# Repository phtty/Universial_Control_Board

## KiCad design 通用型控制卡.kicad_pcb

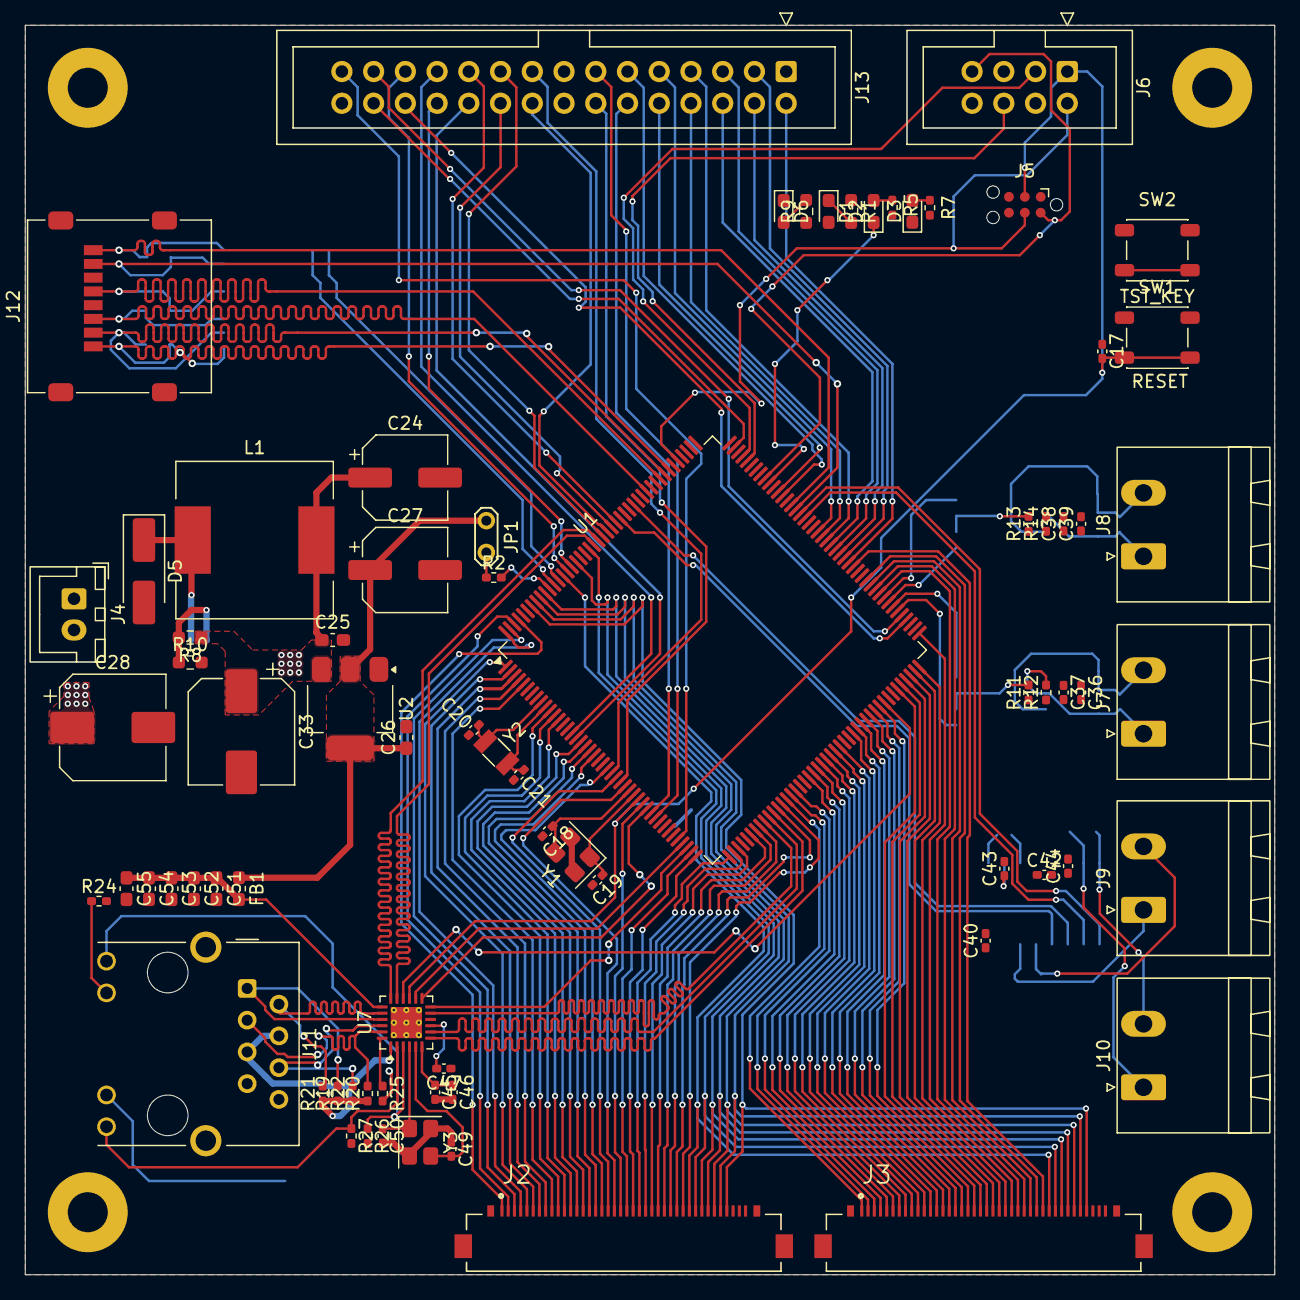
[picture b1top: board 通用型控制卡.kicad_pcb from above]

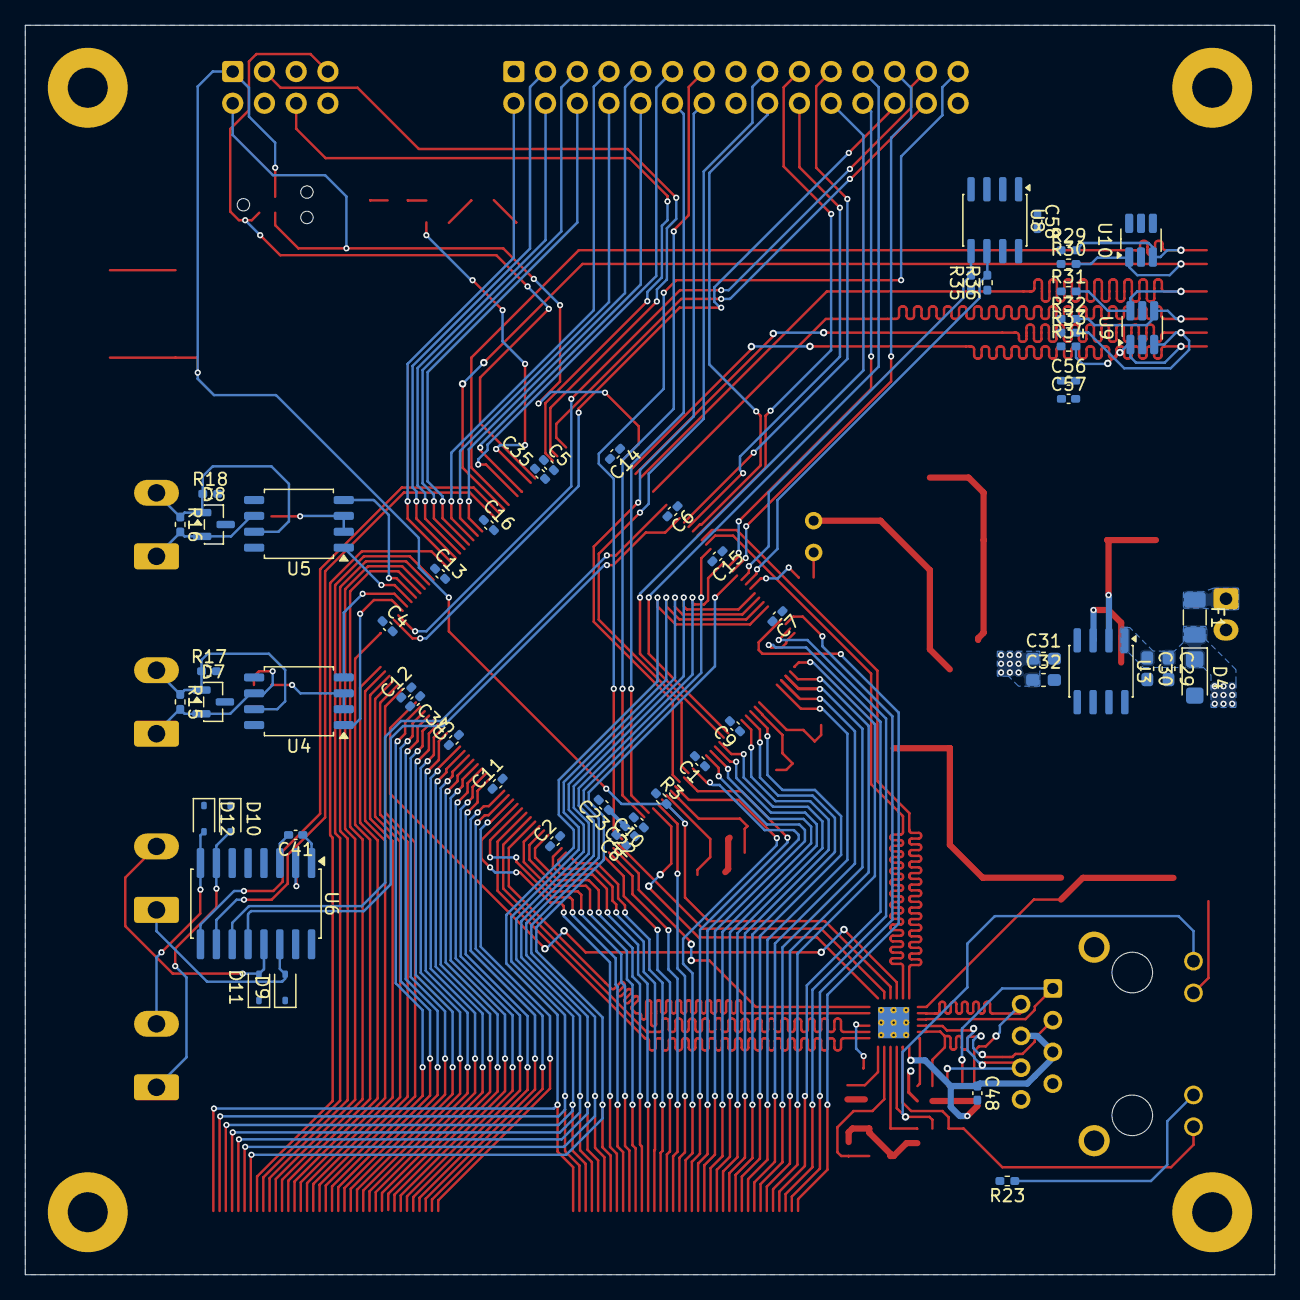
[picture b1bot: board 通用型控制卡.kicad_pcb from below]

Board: 4 copper layers, 100.0 x 100.0 mm, 138 parts (58 on the bottom side), 175 nets.

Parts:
C1, C2, C3, C4, C5, C6, C7, C8, C9, C10, C11, C12, C13, C14, C15, C16, C17, C23, C37, C39, C40, C41, C42, C43, C44, C47, C48, C56, C58: 100nF; C_0402_1005Metric_Pad0.74x0.62mm_HandSolder
C18, C19, C20, C21, C49, C50: 22pF; C_0402_1005Metric_Pad0.74x0.62mm_HandSolder
C22, C34, C35: 2.2uF; C_0402_1005Metric_Pad0.74x0.62mm_HandSolder
C24: 10uF/16V; CP_Elec_6.3x5.9
C25, C26: 100nF/16V; C_0603_1608Metric_Pad1.08x0.95mm_HandSolder
C27: 22uF/16V; CP_Elec_6.3x5.9
C28, C33: 220uF/35V; CP_Elec_8x10
C29: 10uF/35V; C_0603_1608Metric_Pad1.08x0.95mm_HandSolder
C30: 100nF/35V; C_0603_1608Metric_Pad1.08x0.95mm_HandSolder
C31, C51, C53, C54, C55: 100nF; C_0603_1608Metric_Pad1.08x0.95mm_HandSolder
C32: 22uF; C_0603_1608Metric_Pad1.08x0.95mm_HandSolder
C36, C38, C57: 10uF; C_0402_1005Metric_Pad0.74x0.62mm_HandSolder
C45: 471; C_0402_1005Metric_Pad0.74x0.62mm_HandSolder
C46: 1uF; C_0402_1005Metric_Pad0.74x0.62mm_HandSolder
C52: 10uF; C_0603_1608Metric_Pad1.08x0.95mm_HandSolder
D1, D6: GREEN; LED_0603_1608Metric_Pad1.05x0.95mm_HandSolder
D2: RED; LED_0603_1608Metric_Pad1.05x0.95mm_HandSolder
D3: BLUE; LED_0603_1608Metric_Pad1.05x0.95mm_HandSolder
D4: SMF24A; D_SMF
D5: SS34; D_SMA_Handsoldering
D7, D8: SM712; SOT-23
D9, D10, D11, D12: SGSD15C; D_SOD-323
F1: 30V/5A; Fuse_1206_3216Metric
FB1: 330@100Mhz; L_0603_1608Metric_Pad1.05x0.95mm_HandSolder
H1, H2, H3, H4: MountingHole_Pad; MountingHole_3.2mm_M3_Pad
J2: HUB75_A; IPEX_20535-040E-02
J3: HUB75_B; IPEX_20535-040E-02
J4: PWR; JST_XH_B2B-XH-A_1x02_P2.50mm_Vertical
J5: SWD_TC2030; Tag-Connect_TC2030-IDC-NL_2x03_P1.27mm_Vertical
J6: SWD_IDC; IDC-Header_2x04_P2.54mm_Vertical
J7: RS485_1; PhoenixContact_MSTBA_2,5_2-G-5,08_1x02_P5.08mm_Horizontal
J8: RS485_2; PhoenixContact_MSTBA_2,5_2-G-5,08_1x02_P5.08mm_Horizontal
J9: RS232_1; PhoenixContact_MSTBA_2,5_2-G-5,08_1x02_P5.08mm_Horizontal
J10: RS232_2; PhoenixContact_MSTBA_2,5_2-G-5,08_1x02_P5.08mm_Horizontal
J11: RJ45_Hanrun_HR911105A_Horizontal
J12: Micro_SD_Card; microSD_HC_Molex_47219-2001
J13: EXT; IDC-Header_2x15_P2.54mm_Vertical
JP1: BOOT0; TestPoint_2Pads_Pitch2.54mm_Drill0.8mm
L1: 39uH/3.5A; L_12x12mm_H8mm
R1: 4K7; R_0603_1608Metric_Pad0.98x0.95mm_HandSolder
R2, R3, R26, R27, R29, R30, R31, R32, R33, R34: 10K; R_0402_1005Metric_Pad0.72x0.64mm_HandSolder
R5, R7: 1K; R_0402_1005Metric_Pad0.72x0.64mm_HandSolder
R8: 6K8; R_0603_1608Metric_Pad0.98x0.95mm_HandSolder
R9: 10K; R_0603_1608Metric_Pad0.98x0.95mm_HandSolder
R10: 2K2; R_0603_1608Metric_Pad0.98x0.95mm_HandSolder
R11, R12, R13, R14, R17, R18: 360R; R_0402_1005Metric_Pad0.72x0.64mm_HandSolder
R15, R16: 120R; R_0402_1005Metric_Pad0.72x0.64mm_HandSolder
R19, R20, R21, R22: 49R9 1%; R_0402_1005Metric_Pad0.72x0.64mm_HandSolder
R23, R24: 270R; R_0402_1005Metric_Pad0.72x0.64mm_HandSolder
R25: 12K1 1%; R_0402_1005Metric_Pad0.72x0.64mm_HandSolder
R35, R36: 5K1; R_0402_1005Metric_Pad0.72x0.64mm_HandSolder
SW1: RESET; SW_SPST_PTS647_Sx50
SW2: TST_KEY; SW_SPST_PTS647_Sx50
U1: STM32H753IITx; LQFP-176_24x24mm_P0.5mm
U2: LD1117S33TR_SOT223; SOT-223-3_TabPin2
U3: XL1509-ADJ; SOIC-8_3.9x4.9mm_P1.27mm
U4, U5: MAX13487EESA+T; SOIC-8_5.3x5.3mm_P1.27mm
U6: MAX3232; SOIC-16W_5.3x10.2mm_P1.27mm
U7: LAN8742A; VQFN-24-1EP_4x4mm_P0.5mm_EP2.5x2.5mm_ThermalVias
U8: 24LC08; SOIC-8_3.9x4.9mm_P1.27mm
U9, U10: IP4220CZ6; SOT-23-6_Handsoldering
Y1, Y3: 25Mhz; Crystal_SMD_3225-4Pin_3.2x2.5mm
Y2: 32768hz; Crystal_SMD_3215-2Pin_3.2x1.5mm

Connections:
4V5~16V: C28.1, C29.1, C30.1, D4.1 (A1), F1.2, U3.1 (VIN)
+3V3: C1.2, C2.2, C3.2, C4.2, C5.2, C6.2, C7.2, C8.2, C9.2, C10.2, C11.2, C12.2, C13.2, C14.2, C15.2, C16.2, C26.1, C27.1, C40.2, C47.2, C56.1, C57.1, C58.2, D1.2 (A), FB1.1, J2.39, J3.39, J5.1 (VCC), J6.8, J12.4 (VDD), J13.30, JP1.1 (A), R3.1, R5.1, R7.1, R29.1, R30.1, R31.1, R32.1, R33.1, R34.1, R35.1, R36.1, U1.15 (VDD), U1.23 (VDD), U1.36 (VDD), U1.39 (VDDA), U1.49 (VDD), U1.62 (VDD), U1.72 (VDD), U1.82 (VDD), U1.91 (VDD), U1.103 (VDD), U1.114 (VDD33_USB), U1.127 (VDD), U1.136 (VDD), U1.149 (VDD), U1.159 (VDD), U1.171 (PDR_ON), U1.172 (VDD), U2.2 (VO), U6.16 (VCC), U7.9 (VDDIO), U8.8 (VCC), U9.5 (VBUS), U10.5 (VBUS)
+5V: C24.1, C25.1, C31.1, C32.1, C33.1, C36.1, C37.1, C38.1, C39.1, J2.38, J3.38, J13.1, L1.2, R8.1, R9.1, R11.1, R12.1, R13.1, R14.1, U2.3 (VI), U4.8 (VCC), U5.8 (VCC)
/ethernet/ETH_LINK: J11.12, R27.1, U7.2 (LED2/~INTSEL)
/ethernet/ETH_SPD: J11.9, R26.1, U7.3 (LED1/REGOFF)
/ethernet/RJ45_RX+: J11.3 (RD+), R20.2, U7.23 (RXP)
/ethernet/RJ45_RX-: J11.6 (RD-), R22.2, U7.22 (RXN)
/ethernet/RJ45_TX+: J11.1 (TD+), R19.2, U7.21 (TXP)
/ethernet/RJ45_TX-: J11.2 (TD-), R21.2, U7.20 (TXN)
/通用型控制卡/BOOT0: R2.2, U1.166 (BOOT0)
/通用型控制卡/DBG_MCU_RX: J6.3, U1.129 (PH14)
/通用型控制卡/DBG_MCU_TX: J6.6, U1.128 (PH13)
/通用型控制卡/EX_FUN.IIC_SCL: J13.22, U1.17 (PF1)
/通用型控制卡/EX_FUN.IIC_SDA: J13.23, U1.16 (PF0)
/通用型控制卡/EX_FUN.SPI_MISO: J13.20, U1.152 (PG9)
/通用型控制卡/EX_FUN.SPI_MOSI: J13.21, U1.151 (PD7)
/通用型控制卡/EX_FUN.SPI_NSS: J13.18, U1.153 (PG10)
/通用型控制卡/EX_FUN.SPI_SCK: J13.19, U1.154 (PG11)
/通用型控制卡/EX_FUN.UART5_RX: J13.26, U1.92 (PB12)
/通用型控制卡/EX_FUN.UART5_TX: J13.27, U1.93 (PB13)
/通用型控制卡/EX_FUN.UART7_RX: J13.24, U1.161 (PB3)
/通用型控制卡/EX_FUN.UART7_TX: J13.25, U1.162 (PB4)
/通用型控制卡/EX_IO.ADC0: J13.12, U1.34 (PC2_C)
/通用型控制卡/EX_IO.ADC1: J13.13, U1.35 (PC3_C)
/通用型控制卡/EX_IO.ADC2: J13.14, U1.27 (PF9)
/通用型控制卡/EX_IO.ADC3: J13.17, U1.25 (PF7)
/通用型控制卡/EX_IO.IO0: J13.2, U1.105 (PD15)
/通用型控制卡/EX_IO.IO1: J13.3, U1.106 (PG2)
/通用型控制卡/EX_IO.IO2: J13.4, U1.107 (PG3)
/通用型控制卡/EX_IO.IO3: J13.5, U1.108 (PG4)
/通用型控制卡/EX_IO.IO4: J13.6, U1.109 (PG5)
/通用型控制卡/EX_IO.IO5: J13.7, U1.110 (PG6)
/通用型控制卡/EX_IO.IO6: J13.8, U1.111 (PG7)
/通用型控制卡/EX_IO.IO7: J13.9, U1.112 (PG8)
/通用型控制卡/EX_IO.IO8: J13.10, U1.121 (PA10)
/通用型控制卡/EX_IO.IO9: J13.11, U1.120 (PA9)
/通用型控制卡/EX_IO.PWM0: J13.29, U1.40 (PA0)
/通用型控制卡/EX_IO.PWM1: J13.28, U1.131 (PI0)
/通用型控制卡/HUB75.A: J2.34, J3.34, U1.167 (PB8)
/通用型控制卡/HUB75.B: J2.35, J3.35, U1.168 (PB9)
/通用型控制卡/HUB75.B1: J2.3, U1.175 (PI6)
/通用型控制卡/HUB75.B2: J2.6, U1.2 (PE3)
/通用型控制卡/HUB75.B3: J2.9, U1.5 (PE6)
/通用型控制卡/HUB75.B4: J2.12, U1.13 (PI11)
/通用型控制卡/HUB75.B5: J2.15, U1.20 (PF4)
/通用型控制卡/HUB75.B6: J2.18, U1.26 (PF8)
/通用型控制卡/HUB75.B7: J2.21, U1.43 (PH2)
/通用型控制卡/HUB75.B8: J2.24, U1.46 (PH5)
/通用型控制卡/HUB75.B9: J2.27, U1.51 (PA5)
/通用型控制卡/HUB75.B10: J2.30, U1.57 (PB1)
/通用型控制卡/HUB75.B11: J3.3, U1.60 (PF12)
/通用型控制卡/HUB75.B12: J3.6, U1.65 (PF15)
/通用型控制卡/HUB75.B13: J3.9, U1.68 (PE7)
/通用型控制卡/HUB75.B14: J3.12, U1.73 (PE10)
/通用型控制卡/HUB75.B15: J3.15, U1.76 (PE13)
/通用型控制卡/HUB75.B16: J3.18, U1.79 (PB10)
/通用型控制卡/HUB75.B17: J3.21, U1.85 (PH8)
/通用型控制卡/HUB75.B18: J3.24, U1.88 (PH11)
/通用型控制卡/HUB75.B19: J3.27, U1.99 (PD11)
/通用型控制卡/HUB75.B20: J3.30, U1.104 (PD14)
/通用型控制卡/HUB75.C: J2.36, J3.36, U1.169 (PE0)
/通用型控制卡/HUB75.CLK: J2.32, J3.32, U1.157 (PG14)
/通用型控制卡/HUB75.D: J2.37, J3.37, U1.170 (PE1)
/通用型控制卡/HUB75.G1: J2.2, U1.174 (PI5)
/通用型控制卡/HUB75.G2: J2.5, U1.1 (PE2)
/通用型控制卡/HUB75.G3: J2.8, U1.4 (PE5)
/通用型控制卡/HUB75.G4: J2.11, U1.12 (PI10)
/通用型控制卡/HUB75.G5: J2.14, U1.19 (PF3)
/通用型控制卡/HUB75.G6: J2.17, U1.24 (PF6)
/通用型控制卡/HUB75.G7: J2.20, U1.32 (PC0)
/通用型控制卡/HUB75.G8: J2.23, U1.45 (PH4)
/通用型控制卡/HUB75.G9: J2.26, U1.50 (PA4)
/通用型控制卡/HUB75.G10: J2.29, U1.56 (PB0)
/通用型控制卡/HUB75.G11: J3.2, U1.59 (PF11)
/通用型控制卡/HUB75.G12: J3.5, U1.64 (PF14)
/通用型控制卡/HUB75.G13: J3.8, U1.67 (PG1)
/通用型控制卡/HUB75.G14: J3.11, U1.70 (PE9)
/通用型控制卡/HUB75.G15: J3.14, U1.75 (PE12)
/通用型控制卡/HUB75.G16: J3.17, U1.78 (PE15)
/通用型控制卡/HUB75.G17: J3.20, U1.84 (PH7)
/通用型控制卡/HUB75.G18: J3.23, U1.87 (PH10)
/通用型控制卡/HUB75.G19: J3.26, U1.98 (PD10)
/通用型控制卡/HUB75.G20: J3.29, U1.101 (PD13)
/通用型控制卡/HUB75.LAT: J2.33, J3.33, U1.160 (PG15)
/通用型控制卡/HUB75.R1: J2.1, U1.173 (PI4)
/通用型控制卡/HUB75.R2: J2.4, U1.176 (PI7)
/通用型控制卡/HUB75.R3: J2.7, U1.3 (PE4)
/通用型控制卡/HUB75.R4: J2.10, U1.11 (PI9)
/通用型控制卡/HUB75.R5: J2.13, U1.18 (PF2)
/通用型控制卡/HUB75.R6: J2.16, U1.21 (PF5)
/通用型控制卡/HUB75.R7: J2.19, U1.28 (PF10)
/通用型控制卡/HUB75.R8: J2.22, U1.44 (PH3)
/通用型控制卡/HUB75.R9: J2.25, U1.47 (PA3)
/通用型控制卡/HUB75.R10: J2.28, U1.52 (PA6)
/通用型控制卡/HUB75.R11: J3.1, U1.58 (PB2)
/通用型控制卡/HUB75.R12: J3.4, U1.63 (PF13)
/通用型控制卡/HUB75.R13: J3.7, U1.66 (PG0)
/通用型控制卡/HUB75.R14: J3.10, U1.69 (PE8)
/通用型控制卡/HUB75.R15: J3.13, U1.74 (PE11)
/通用型控制卡/HUB75.R16: J3.16, U1.77 (PE14)
/通用型控制卡/HUB75.R17: J3.19, U1.83 (PH6)
/通用型控制卡/HUB75.R18: J3.22, U1.86 (PH9)
/通用型控制卡/HUB75.R19: J3.25, U1.89 (PH12)
/通用型控制卡/HUB75.R20: J3.28, U1.100 (PD12)
/通用型控制卡/HUB75.~OE: J2.31, J3.31, U1.163 (PB5)
/通用型控制卡/OSC32_IN: C20.2, U1.9 (PC14), Y2.2
/通用型控制卡/OSC32_OUT: C21.1, U1.10 (PC15), Y2.1
/通用型控制卡/OSC_IN: C18.2, U1.29 (PH0), Y1.3
/通用型控制卡/OSC_OUT: C19.1, U1.30 (PH1), Y1.1
/通用型控制卡/SWCLK: J5.4 (SWCLK), J6.2, U1.137 (PA14)
/通用型控制卡/SWDIO: J5.2 (SWDIO), J6.7, U1.124 (PA13)
/通用型控制卡/TST_KEY: SW2.2, U1.122 (PA11)
/通用型控制卡/~LED_STA_ERR: D2.1 (K), U1.123 (PA12)
/通用型控制卡/~LED_STA_RUN: D3.1 (K), U1.119 (PA8)
EEPROM.SCL: R36.2, U1.165 (PB7), U8.6 (SCL)
EEPROM.SDA: R35.2, U1.164 (PB6), U8.5 (SDA)
ETH.CRS_DV: U1.53 (PA7), U7.11 (CRS_DV/MODE2)
ETH.MDC: U1.33 (PC1), U7.13 (MDC)
ETH.MDIO: U1.42 (PA2), U7.12 (MDIO)
ETH.REF_CLK: U1.41 (PA1), U7.14 (~INT/REFCLKO)
ETH.RXD0: U1.54 (PC4), U7.8 (RXD0/MODE0)
ETH.RXD1: U1.55 (PC5), U7.7 (RXD1/MODE1)
ETH.TXD0: U1.156 (PG13), U7.17 (TXD0)
ETH.TXD1: U1.155 (PG12), U7.18 (TXD1)
ETH.TX_EN: U1.80 (PB11), U7.16 (TXEN)
ETH_VDD: C48.1, C51.1, C52.1, C53.1, C54.1, C55.1, FB1.2, J11.4 (TCT), J11.5 (RCT), R19.1, R20.1, R21.1, R22.1, U7.1 (VDD2A), U7.19 (VDD1A)
GND: C1.1, C2.1, C3.1, C4.1, C5.1, C6.1, C7.1, C8.1, C9.1, C10.1, C11.1, C12.1, C13.1, C14.1, C15.1, C16.1, C17.1, C18.1, C19.2, C20.1, C21.2, C22.1, C23.2, C24.2, C25.2, C26.2, C27.2, C28.2, C29.2, C30.2, C31.2, C32.2, C33.2, C34.1, C35.1, C36.2, C37.2, C38.2, C39.2, C40.1, C43.2, C44.2, C45.2, C46.2, C47.1, C48.2, C49.1, C50.2, C51.2, C52.2, C53.2, C54.2, C55.2, C56.2, C57.2, C58.1, D4.2 (A2), D5.2 (A), D6.1 (K), D7.3 (common), D8.3 (common), D9.1 (A1), D10.1 (A1), D11.1 (A1), D12.1 (A1), H1.1 (1_1), H2.1 (1_1), H3.1 (1_1), H4.1 (1_1), J2.40, J2.S1 (SHIELD), J2.S2 (SHIELD), J2.S3 (SHIELD), J2.S4 (SHIELD), J3.40, J3.S1 (SHIELD), J3.S2 (SHIELD), J3.S3 (SHIELD), J3.S4 (SHIELD), J4.2, J5.5 (GND), J6.4, J6.5, J11.8, J11.SH, J12.6 (VSS), J12.SH (SHIELD), J13.15, J13.16, R1.1, R10.2, R17.2, R18.2, R23.2, R24.2, R25.2, R26.2, R27.2, SW1.1, SW2.1, U1.14 (VSS), U1.22 (VSS), U1.37 (VSSA), U1.48 (VSS), U1.61 (VSS), U1.71 (VSS), U1.90 (VSS), U1.102 (VSS), U1.113 (VSS), U1.126 (VSS), U1.135 (VSS), U1.148 (VSS), U1.158 (VSS), U2.1 (GND), U3.4 (~EN), U3.5 (GND), U3.6 (GND), U3.7 (GND), U3.8 (GND), U4.5 (GND), U5.5 (GND), U6.15 (GND), U7.25 (VSS), U8.1 (A0), U8.2 (A1), U8.3 (A2), U8.4 (GND), U8.7 (WP), U9.2 (GND), U10.2 (GND), Y1.2 (G), Y1.4 (G), Y3.2 (G), Y3.4 (G)
unnamed: C34.2, U1.81 (VCAP)
unnamed: C35.2, U1.125 (VCAP)
unnamed: D1.1 (K), R1.2
unnamed: D2.2 (A), R5.2
unnamed: D3.2 (A), R7.2
unnamed: D5.1 (K), L1.1, U3.2 (OUT)
unnamed: D6.2 (A), R9.2
unnamed: D7.1 (A1), J7.2, R15.1, R17.1, U4.7 (B)
unnamed: D7.2 (A2), J7.1, R12.2, R15.2, U4.6 (A)
unnamed: D8.1 (A1), J8.2, R16.1, R18.1, U5.7 (B)
unnamed: D8.2 (A2), J8.1, R14.2, R16.2, U5.6 (A)
unnamed: D9.2 (A2), J9.1, U6.14 (T1OUT)
unnamed: D10.2 (A2), J10.1, U6.7 (T2OUT)
unnamed: D11.2 (A2), J9.2, U6.13 (R1IN)
unnamed: D12.2 (A2), J10.2, U6.8 (R2IN)
unnamed: F1.1, J4.1
unnamed: J11.10, R24.1
unnamed: J11.11, R23.1
unnamed: JP1.2 (B), R2.1
unnamed: R8.2, R10.1, U3.3 (FB)
unnamed: R11.2, U4.2 (~RE), U4.3 (~SHDN)
unnamed: R13.2, U5.2 (~RE), U5.3 (~SHDN)
unnamed: C41.1, U6.1 (C1+)
unnamed: C41.2, U6.3 (C1-)
unnamed: C42.1, U6.4 (C2+)
unnamed: C42.2, U6.5 (C2-)
unnamed: C43.1, U6.2 (VS+)
unnamed: C44.1, U6.6 (VS-)
unnamed: R25.1, U7.24 (RBIAS)
unnamed: C45.1, C46.1, U7.6 (VDDCR)
unnamed: C49.2, U7.5 (XTAL1/CLKIN), Y3.3
unnamed: C50.1, U7.4 (XTAL2), Y3.1
RS232.RX1: U1.150 (PD6), U6.12 (R1OUT)
RS232.RX2: U1.116 (PC7), U6.9 (R2OUT)
RS232.TX1: U1.147 (PD5), U6.11 (T1IN)
RS232.TX2: U1.115 (PC6), U6.10 (T2IN)
RS485.RX1: U1.95 (PB15), U4.4 (DI)
RS485.RX2: U1.97 (PD9), U5.4 (DI)
RS485.TX1: U1.94 (PB14), U4.1 (RO)
RS485.TX2: U1.96 (PD8), U5.1 (RO)
SDMMC.CK: J12.5 (CLK), R31.2, U1.141 (PC12), U9.6 (I/O4)
SDMMC.CMD: J12.3 (CMD), R32.2, U1.144 (PD2), U9.4 (I/O3)
SDMMC.D0: J12.7 (DAT0), R30.2, U1.117 (PC8), U10.1 (I/O1)
SDMMC.D1: J12.8 (DAT1), R29.2, U1.118 (PC9), U10.3 (I/O2)
SDMMC.D2: J12.1 (DAT2), R34.2, U1.139 (PC10), U9.1 (I/O1)
SDMMC.D3: J12.2 (DAT3/CD), R33.2, U1.140 (PC11), U9.3 (I/O2)
VREF: C22.2, C23.1, U1.38 (VREF+)
~RST: C17.2, J5.3 (~RESET), J6.1, R3.2, SW1.2, U1.31 (NRST), U7.15 (~RST)

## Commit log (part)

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2026-06-10 首次提交
2026-06-10 style: 修改图框
2026-06-11 feat: 添加了安装孔
2026-06-12 调整部分元件属性
2026-06-24 feat: 布局完成，正在布线
2026-06-24 feat: 布线完成
